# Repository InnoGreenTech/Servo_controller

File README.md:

# Servo_controller
This is a controller of servomotors, it is configurable by serial port, without programmation

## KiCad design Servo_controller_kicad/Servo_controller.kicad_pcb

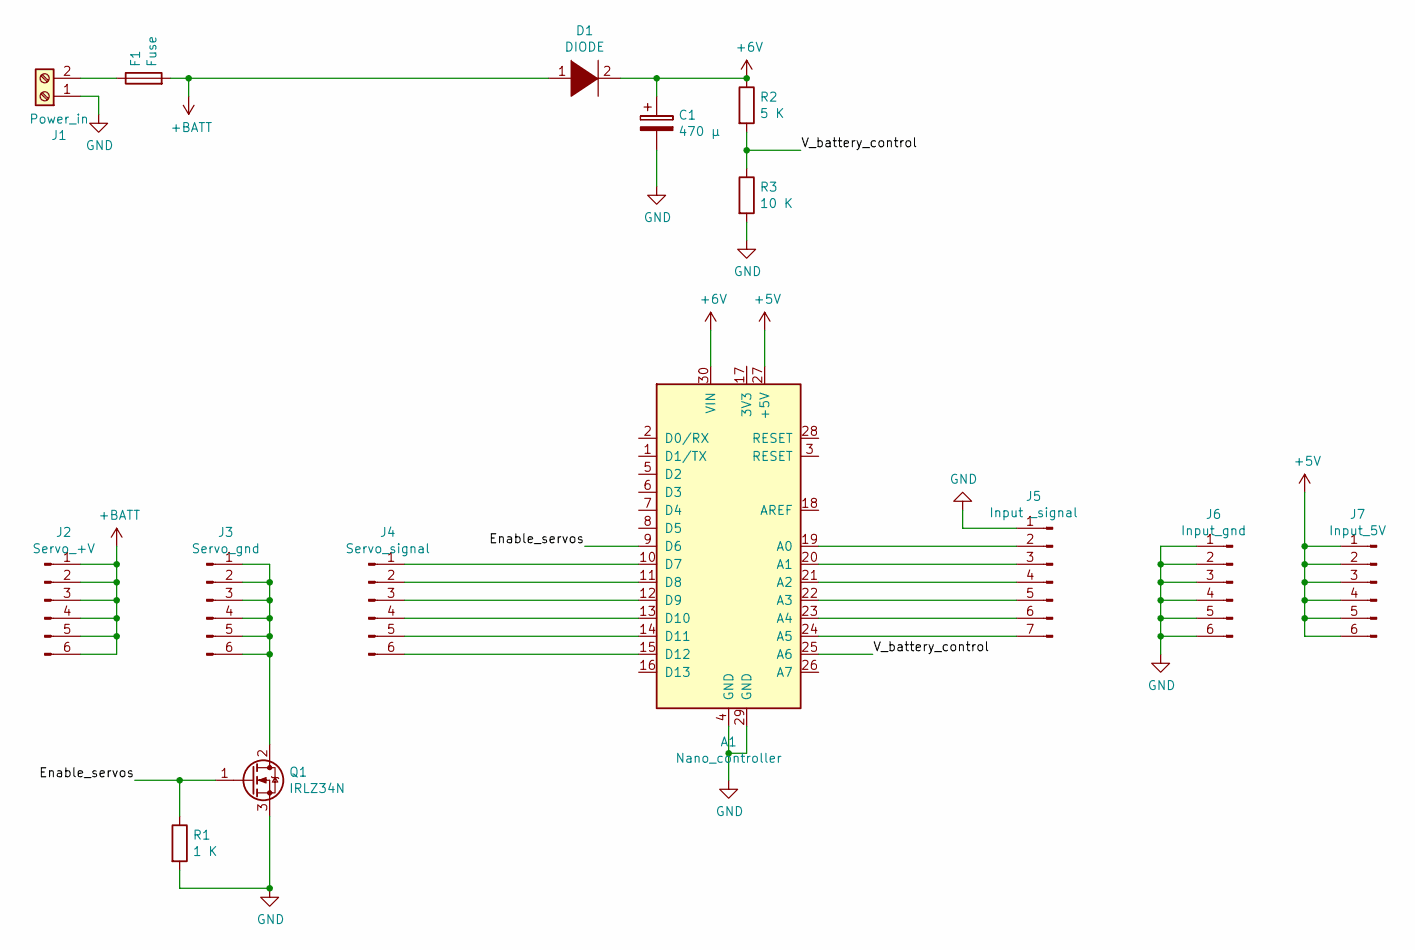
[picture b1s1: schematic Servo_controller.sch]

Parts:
A1: Nano_controller; Arduino_Nano
C1: 470 µ; CP_Radial_D7.5mm_P2.50mm
D1: DIODE; D_DO-15_P10.16mm_Horizontal
F1: Fuse; Fuse_Littelfuse_395Series
J1: Power_in; TerminalBlock_bornier-2_P5.08mm
J2: Servo_+V; PinSocket_1x06_P2.54mm_Vertical
J3: Servo_gnd; PinSocket_1x06_P2.54mm_Vertical
J4: Servo_signal; PinSocket_1x06_P2.54mm_Vertical
J5: Input _signal; PinSocket_1x07_P2.54mm_Vertical
J6: Input_gnd; PinSocket_1x06_P2.54mm_Vertical
J7: Input_5V; PinSocket_1x06_P2.54mm_Vertical
Q1: IRLZ34N; TO-220-3_Vertical
R1: 1 K; R_Axial_DIN0207_L6.3mm_D2.5mm_P7.62mm_Horizontal
R2: 5 K; R_Axial_DIN0207_L6.3mm_D2.5mm_P7.62mm_Horizontal
R3: 10 K; R_Axial_DIN0207_L6.3mm_D2.5mm_P7.62mm_Horizontal

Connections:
+5V: A1.27 (+5V), J7.1, J7.2, J7.3, J7.4, J7.5, J7.6
+6V: A1.30 (VIN), C1.1, D1.2 (A), R2.1
+BATT: D1.1 (K), F1.2, J2.1, J2.2, J2.3, J2.4, J2.5, J2.6
/Enable_servos: A1.9 (D6), Q1.1 (G), R1.1
/V_battery_control: A1.25 (A6), R2.2, R3.1
GND: A1.4 (GND), A1.29 (GND), C1.2, J1.1, J5.1, J6.1, J6.2, J6.3, J6.4, J6.5, J6.6, Q1.3 (S), R1.2, R3.2
unnamed: A1.10 (D7), J4.1
unnamed: A1.11 (D8), J4.2
unnamed: A1.12 (D9), J4.3
unnamed: A1.13 (D10), J4.4
unnamed: A1.14 (D11), J4.5
unnamed: A1.15 (D12), J4.6
unnamed: A1.19 (A0), J5.2
unnamed: A1.20 (A1), J5.3
unnamed: A1.21 (A2), J5.4
unnamed: A1.22 (A3), J5.5
unnamed: A1.23 (A4), J5.6
unnamed: A1.24 (A5), J5.7
unnamed: F1.1, J1.2
unnamed: J3.1, J3.2, J3.3, J3.4, J3.5, J3.6, Q1.2 (D)

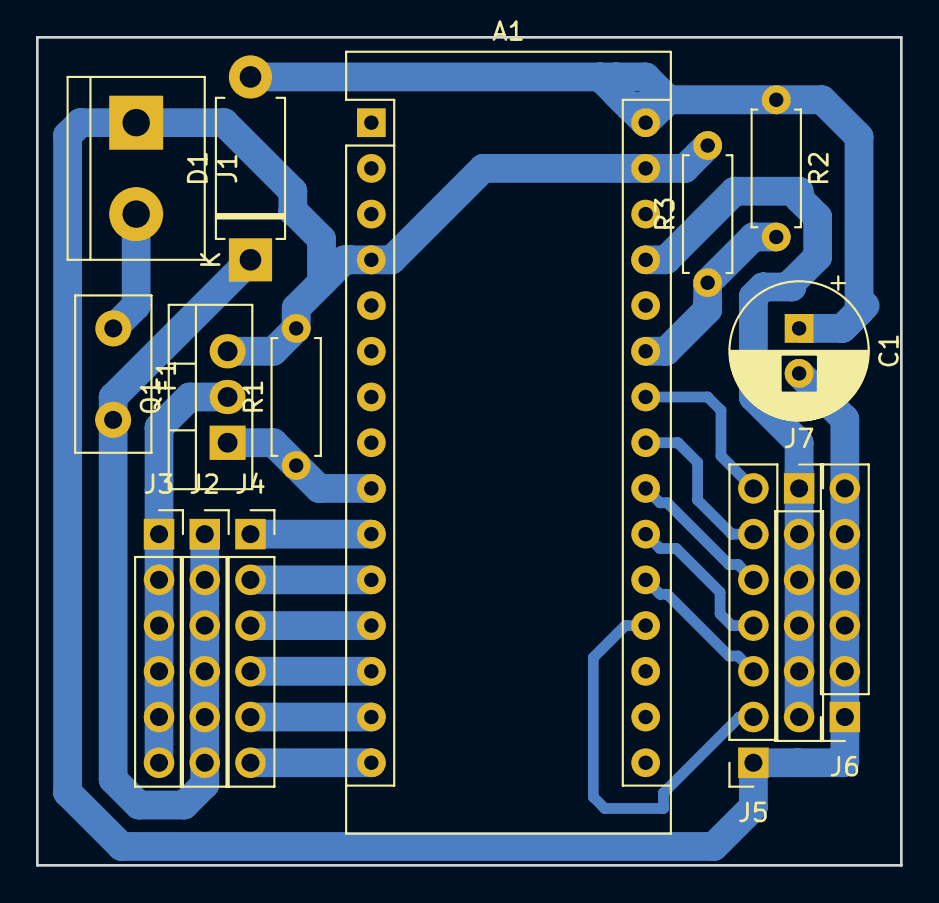
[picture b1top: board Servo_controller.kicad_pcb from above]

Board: 2 copper layers, 48.0 x 46.0 mm, 15 parts (0 on the bottom side), 20 nets.

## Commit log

2020-10-31 add a new mode to control the servo
2020-11-01 Update hepl file in line
2020-11-01 cleaning code
2020-11-06 Add new impulse mode
2020-12-06 set bug ar the first row
